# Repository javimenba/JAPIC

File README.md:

# JAPIC: Placa en desarrollo para pic18f45k50. 
 
## Índice de contenidos
* [Schematic](#item1)
    * [Módulo de alimentación, regulador, control y salida](#item3)
    * [Puerto de salida y entrada del PIC18F45K50](#item4)
    * [Integración de módulos](#item5)
* [PCB](#item2)
    * [F.Cu](#item9)
    * [B.Cu](#item7)
    * [Vista 3D](#item8)
* [Final](#item9)    

### Schematic
 
Se presenta la segunda versión de la placa ***JAPIC*** visualizando su Schequetic:

[Subir](#top) 

 **Alimentación, regulador, control y salida:**

[Subir](#top)

**Puerto de salida y entrada del PIC18F45K50:**

[Subir](#top)

**Integración de módulos:**

 [Subir](#top)

### PCB

[Subir](#top)

**B.Cu:**

[Subir](#top)

**F.Cu:**

[Subir](#top)

**Vista 3D:**

[Subir](#top)

**Final:**

[Subir](#top)

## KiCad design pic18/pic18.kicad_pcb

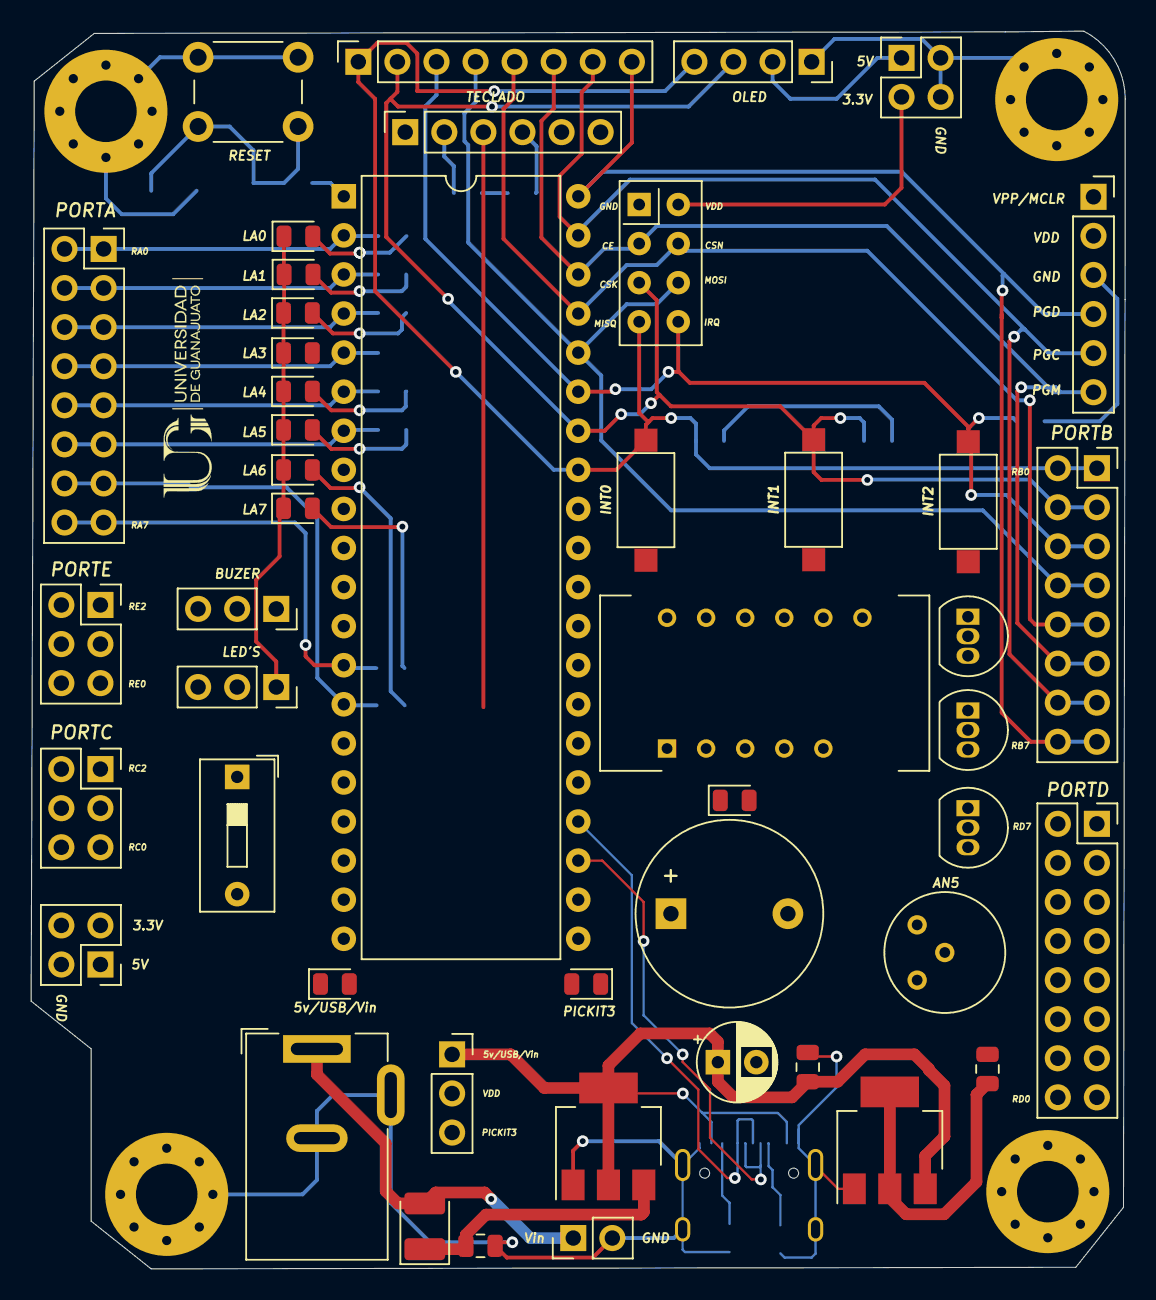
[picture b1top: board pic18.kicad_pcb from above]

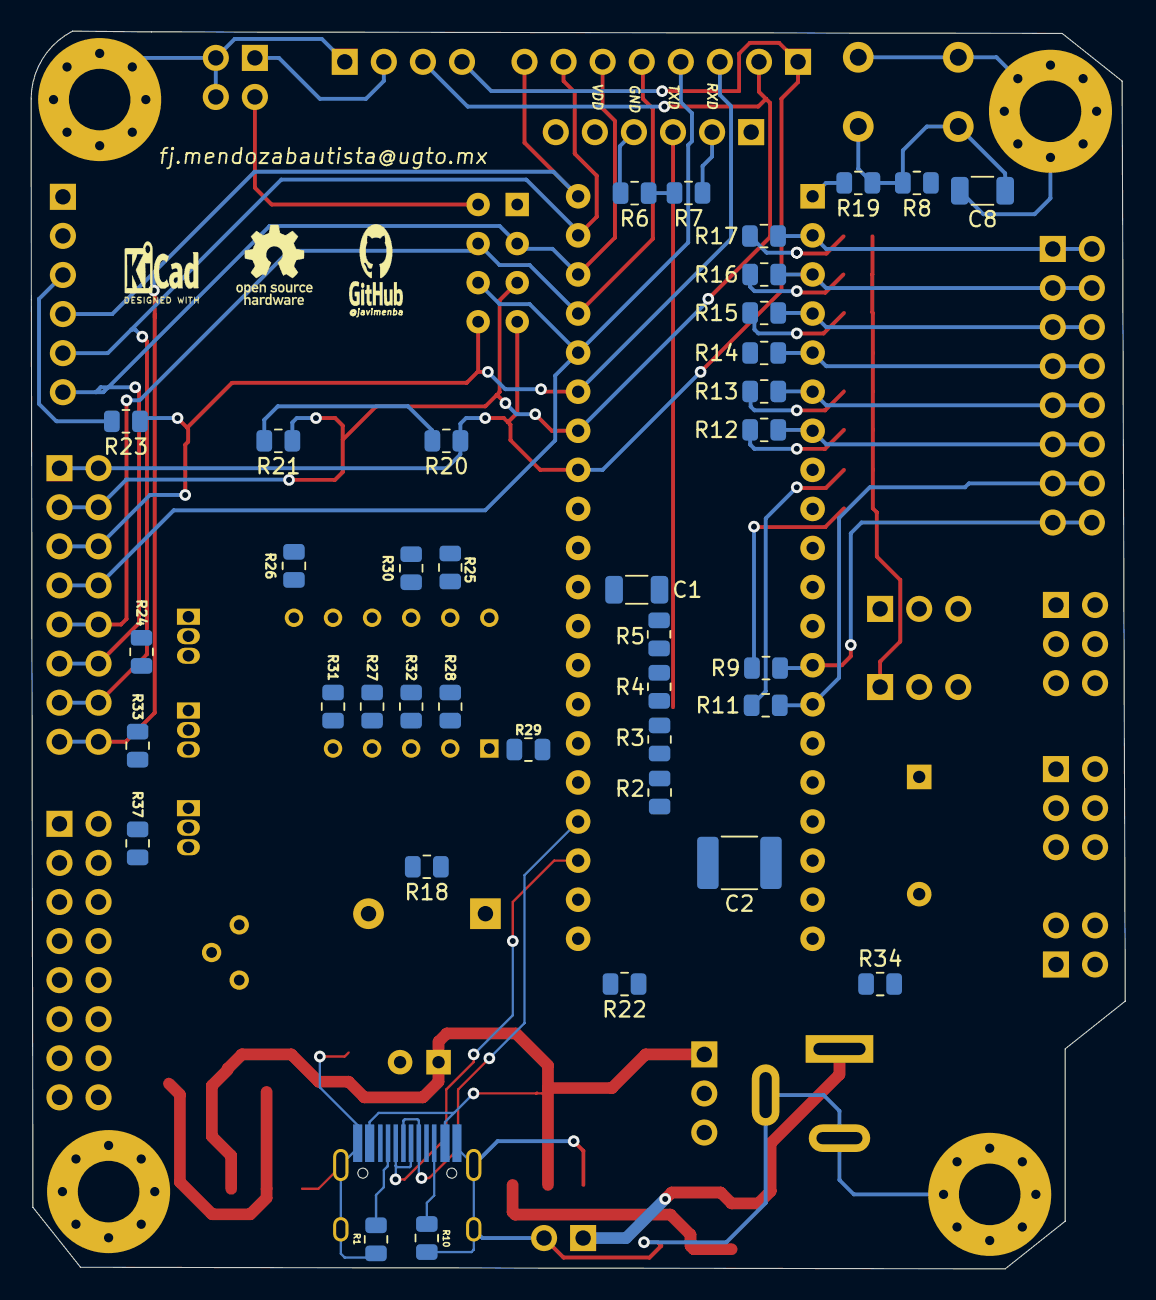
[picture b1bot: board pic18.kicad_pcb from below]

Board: 2 copper layers, 71.1 x 80.4 mm, 96 parts (42 on the bottom side), 79 nets.

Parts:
BZ1: Buzzer; Buzzer_12x9.5RM7.6
C1, C8: 100nf; C_1206_3216Metric
C2: 220nf; C_1812_4532Metric
C3: 100uF; CP_Radial_D5.0mm_P2.50mm
C4, C5, C9: 0.1uF; C_0805_2012Metric
D1, D12, D13: LED; LED_0805_2012Metric
D4: LED4; LED_0805_2012Metric
D5, D11: LED11; LED_0805_2012Metric
D6: LED6; LED_0805_2012Metric
D7: LED7; LED_0805_2012Metric
D8: LED8; LED_0805_2012Metric
D9: LED9; LED_0805_2012Metric
D10: LED10; LED_0805_2012Metric
D14: 1N4007; D_1210_3225Metric_Pad1.42x2.65mm_HandSolder
DIG1, DIG2, DIG3: 2N2219; TO-92_Inline
G1: LOGO; github
G2: LOGO; open_hardware
G3: LOGO; kicad_logo
G4: LOGO; abeja_sf
G5: LOGO; fimee
G6: LOGO; usb_logo
H1: 1; MountingHole_4mm_Pad_Via
H2: 2; MountingHole_4mm_Pad_Via
H3: 3; MountingHole_4mm_Pad_Via
H4: 4; MountingHole_4mm_Pad_Via
INT0, INT1, INT2: SW_Push; SW_SPST_CK_RS282G05A3
J1: PORTA; PinSocket_2x08_P2.54mm_Vertical
J2: PORTB; PinSocket_2x08_P2.54mm_Vertical
J3: Barrel_Jack_Switch; BarrelJack_Wuerth_6941xx301002
J4: Vin; PinHeader_1x02_P2.54mm_Vertical
J5: TECLADO; PinSocket_1x08_P2.54mm_Vertical
J6: OLED; PinSocket_1x04_P2.54mm_Vertical
J7: PORTD; PinSocket_2x08_P2.54mm_Vertical
J8: HC-05; PinSocket_1x06_P2.54mm_Vertical
J9: PORTC; PinSocket_2x03_P2.54mm_Vertical
J10: PORTE; PinSocket_2x03_P2.54mm_Vertical
J11, J12: 5v-3.3v; PinSocket_2x02_P2.54mm_Vertical
J14: PICKIT3; PinSocket_1x06_P2.54mm_Vertical
J15: CONTROL; PinSocket_1x03_P2.54mm_Vertical
J20: LED'S; PinSocket_1x03_P2.54mm_Vertical
J21: BUZZER; PinSocket_1x03_P2.54mm_Vertical
R1, R10: 5.1k; R_0805_2012Metric
R2, R3, R4, R5: 4.7; R_0805_2012Metric
R6: 2K; R_0805_2012Metric
R7, R25, R26, R27, R28, R29, R30, R31, R32: 1K; R_0805_2012Metric
R8, R20, R21, R23: 10k; R_0805_2012Metric
R9, R11, R12, R13, R14, R15, R16, R17, R18, R22: 220; R_0805_2012Metric
R19, R34: 470; R_0805_2012Metric
R24, R33, R37: 10K; R_0805_2012Metric
RV1: R_POT_TRIM; Potentiometer_Bourns_3339H_Vertical
SW1: SW_Push; SW_PUSH_6mm
SW2: SW_DIP_x01; SW_DIP_SPSTx01_Slide_9.78x4.72mm_W7.62mm_P2.54mm
U1: PIC18F45K50; DIP-40_W15.24mm
U2: 3x7Segment; 3x7SEGMENT-04x08-Red
U3: NRF24L01_Breakout; nRF24L01_Breakout
U4: AMS1117-5.0; SOT-223-3_TabPin2
U5: AMS1117-3.3; SOT-223-3_TabPin2
USB1: HRO-TYPE-C-31-M-12; HRO-TYPE-C-31-M-12-HandSoldering

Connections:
3.3v: C5.1, J11.2, J12.2, U3.2, U5.2
5V: C3.1, C4.1, D1.2, J15.1, U4.2, U5.3, USB1.2, USB1.11
/3V3: C2.1, U1.18
/DIG1: DIG1.3, U2.12
/DIG2: DIG2.3, U2.9
/DIG3: DIG3.3, U2.8
/GND1: D4.1, D5.1, D6.1, D7.1, D8.1, D9.1, D10.1, D11.1, J20.1
/MCLR: J14.1, R19.2, U1.1
/RA0: J1.1, J1.2, R17.1, U1.2
/RA1: J1.3, J1.4, R16.1, U1.3
/RA2: J1.5, J1.6, R15.1, U1.4
/RA3: J1.7, J1.8, R14.1, U1.5
/RA4: J1.9, J1.10, R13.1, U1.6
/RA5: J1.11, J1.12, R12.1, U1.7
/RA6: J1.13, J1.14, R11.1, U1.14
/RA7: J1.15, J1.16, R9.1, U1.13
/RB0: INT0.2, J2.1, J2.2, J5.1, J6.4, R20.1, U1.33, U3.7
/RB1: INT1.2, J2.3, J2.4, J5.2, J6.3, R21.1, U1.34, U3.5
/RB2: INT2.2, J2.5, J2.6, J5.3, R23.1, U1.35, U3.8
/RB3: J2.7, J2.8, J5.4, U1.36, U3.6
/RB4: J2.9, J2.10, J5.5, U1.37, U3.4
/RB5: J2.11, J2.12, J5.6, J14.6, U1.38, U3.3
/RB6: J2.13, J2.14, J5.7, J14.5, U1.39
/RB7: J2.15, J2.16, J5.8, J14.4, U1.40
/RC0: J9.1, J9.2, U1.15
/RC1: J9.3, J9.4, U1.16
/RC2: J9.5, J9.6, U1.17
/RC4: U1.23, USB1.5, USB1.7
/RC5: U1.24, USB1.6, USB1.8
/RC6: R6.1, R7.2, U1.25
/RC7: J8.3, U1.26
/RD0: J7.1, J7.2, R31.2, U1.19
/RD1: J7.3, J7.4, R30.2, U1.20
/RD2: J7.5, J7.6, R29.2, U1.21
/RD3: J7.7, J7.8, R28.2, U1.22
/RD4: J7.9, J7.10, R27.2, U1.27
/RD5: J7.11, J7.12, R26.2, U1.28
/RD6: J7.13, J7.14, R25.2, U1.29
/RD7: J7.15, J7.16, R32.2, U1.30
/RE0: J10.1, J10.2, R24.2, SW2.2, U1.8
/RE1: J10.3, J10.4, J21.1, R18.1, R33.2, U1.9
/RE2: J10.5, J10.6, R37.2, U1.10
/TX: J8.2, R7.1
/Vin: D14.2, J3.1, J4.1
GND: BZ1.2, C1.2, C2.2, C3.2, C4.2, C5.2, C8.2, C9.2, D12.1, D13.1, DIG1.1, DIG2.1, DIG3.1, H1.1, H2.1, H3.1, H4.1, J3.2, J3.3, J4.2, J6.1, J8.4, J11.3, J11.4, J12.3, J12.4, J14.3, J20.2, R1.1, R6.2, R10.1, R20.2, R21.2, R23.2, R34.2, RV1.3, SW1.1, U1.12, U1.31, U3.1, U4.1, U5.1, USB1.1, USB1.12, USB1.13
unnamed: BZ1.1, J21.2
unnamed: C1.1, R5.2, U1.11
unnamed: C8.1, R8.2, R19.1, SW1.2
unnamed: C9.1, D14.1, U4.3
unnamed: D1.1, R34.1
unnamed: D4.2, R9.2
unnamed: D5.2, R11.2
unnamed: D6.2, R12.2
unnamed: D7.2, R13.2
unnamed: D8.2, R14.2
unnamed: D9.2, R15.2
unnamed: D10.2, R16.2
unnamed: D11.2, R17.2
unnamed: D12.2, R18.2
unnamed: D13.2, R22.2
unnamed: DIG1.2, R24.1
unnamed: DIG2.2, R33.1
unnamed: DIG3.2, R37.1
unnamed: R1.2, USB1.4
unnamed: R2.2, R3.1
unnamed: R3.2, R4.1
unnamed: R4.2, R5.1
unnamed: R10.2, USB1.10
unnamed: R25.1, U2.11
unnamed: R26.1, U2.7
unnamed: R27.1, U2.4
unnamed: R28.1, U2.2
unnamed: R29.1, U2.1
unnamed: R30.1, U2.10
unnamed: R31.1, U2.5
unnamed: R32.1, U2.3
unnamed: RV1.2, SW2.1
VDD: INT0.1, INT1.1, INT2.1, J6.2, J8.5, J11.1, J12.1, J15.2, R2.1, R8.1, RV1.1
VPICKIT3: J14.2, J15.3, R22.1

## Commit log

2020-11-18 javimenba
2021-06-28 JaPic
